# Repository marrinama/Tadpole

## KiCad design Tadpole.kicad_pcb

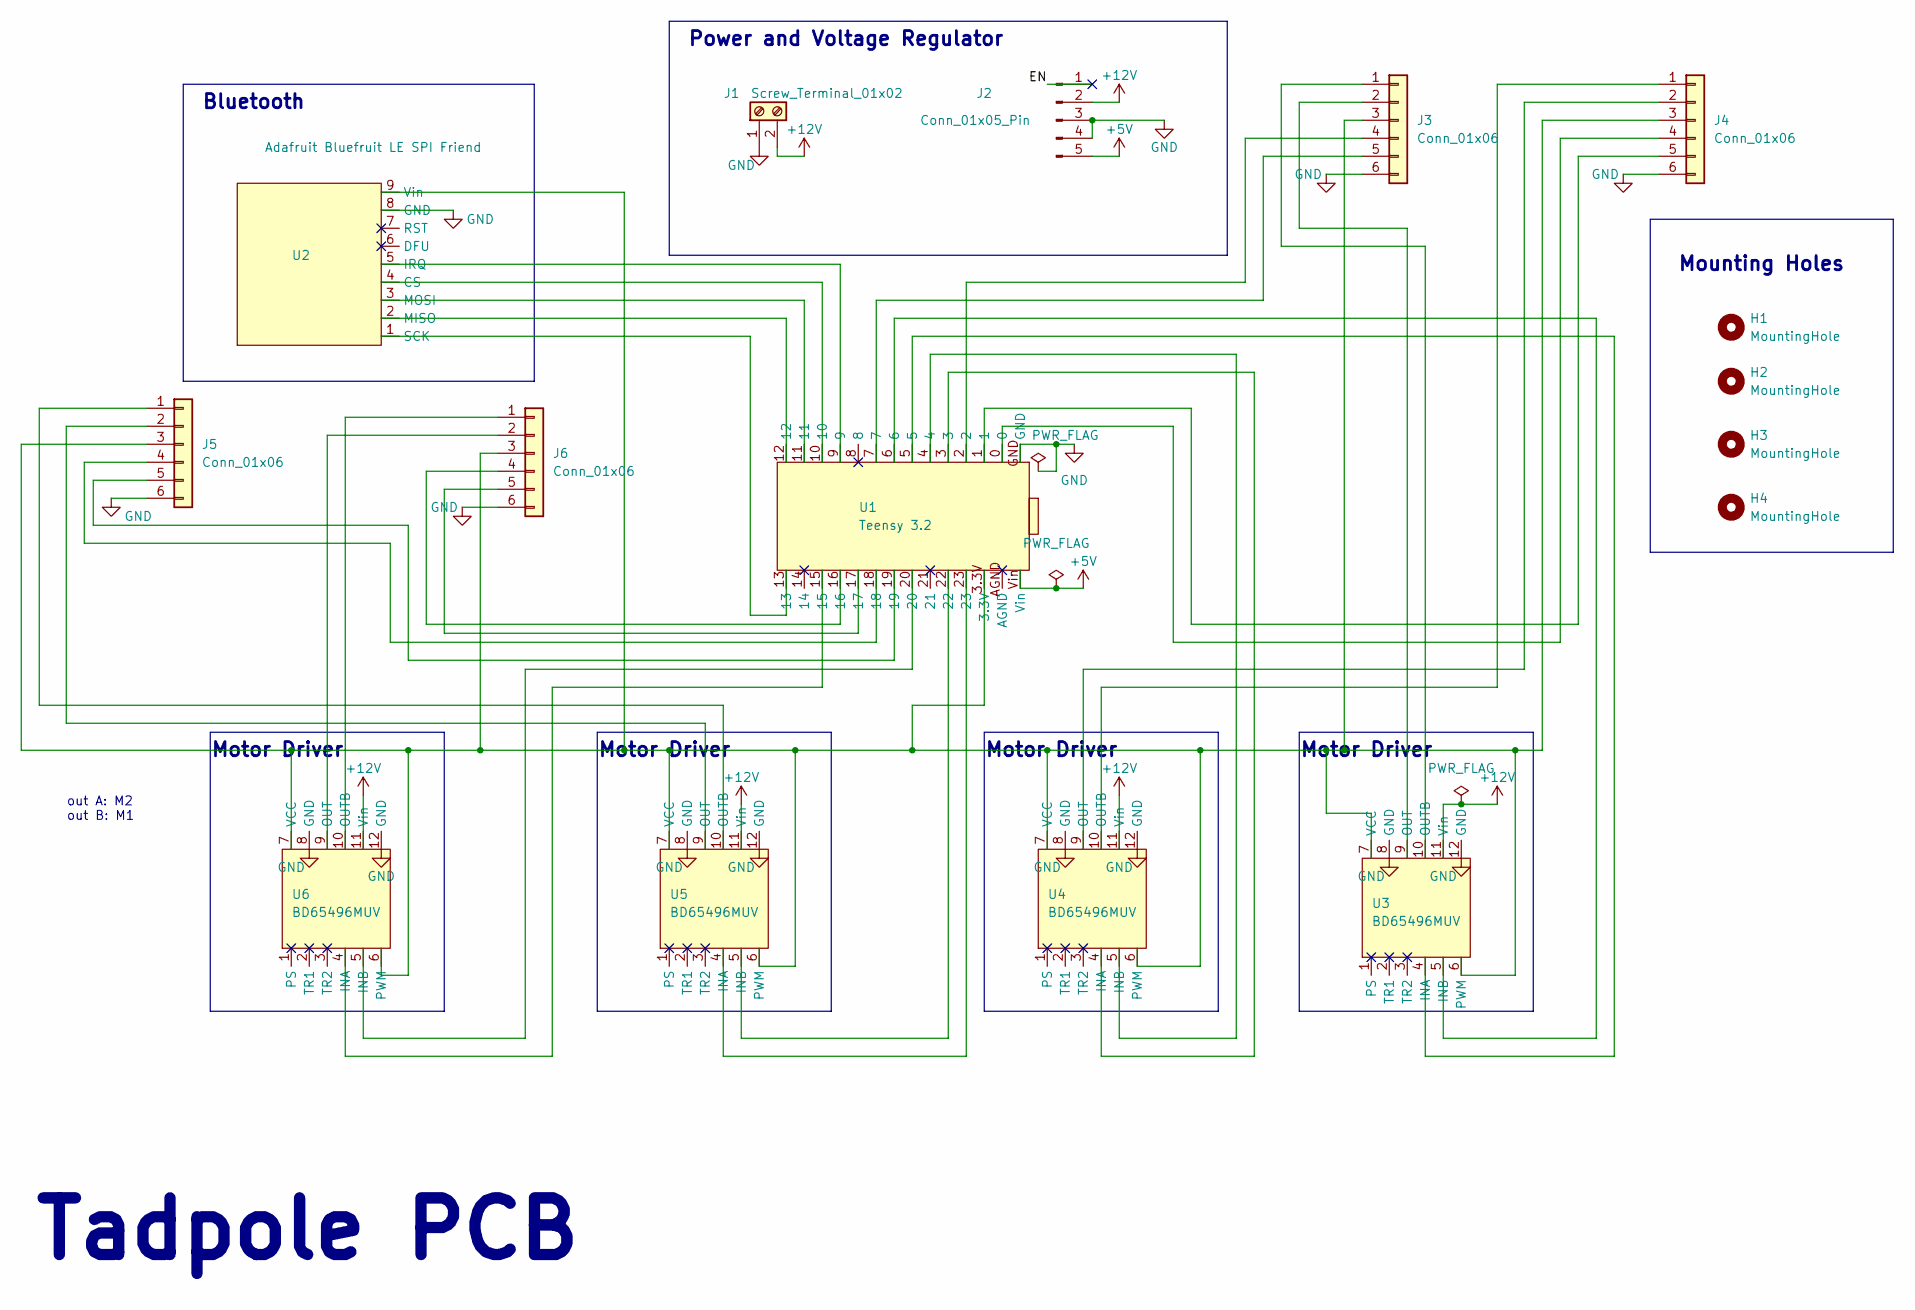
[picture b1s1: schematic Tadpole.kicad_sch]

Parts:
H1, H2, H3, H4: MountingHole; MountingHole_2.2mm_M2_DIN965_Pad
J1: Screw_Terminal_01x02; AMASS_XT30U-M_1x02_P5.0mm_Vertical
J2: Conn_01x05_Pin; PinHeader_1x05_P2.54mm_Vertical
J3, J4, J5, J6: Conn_01x06; PinHeader_1x06_P2.54mm_Vertical
U1: Teensy 3.2; teensy
U2: Adafruit Bluefruit LE SPI Friend
U3, U4, U5, U6: BD65496MUV

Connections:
+5V: J2.5, U1.Vin
+12V: J1.2, J2.2, U3.11 (Vin), U4.11 (Vin), U5.11 (Vin), U6.11 (Vin)
/EN: J2.1
GND: J1.1, J2.3, J2.4, J3.6, J4.6, J5.6, J6.6, U1.GND, U2.8 (GND), U3.8 (GND), U3.12 (GND), U4.8 (GND), U4.12 (GND), U5.8 (GND), U5.12 (GND), U6.8 (GND), U6.12 (GND)
unnamed: J3.1, U3.10 (OUTB)
unnamed: J3.2, U3.9 (OUT)
unnamed: J3.3, J4.3, J5.3, J6.3, U1.3.3V, U2.9 (Vin), U3.6 (PWM), U3.7 (VCC), U4.6 (PWM), U4.7 (VCC), U5.6 (PWM), U5.7 (VCC), U6.6 (PWM), U6.7 (VCC)
unnamed: J3.4, U1.2
unnamed: J3.5, U1.7
unnamed: J4.1, U4.10 (OUTB)
unnamed: J4.2, U4.9 (OUT)
unnamed: J4.4, U1.0
unnamed: J4.5, U1.1
unnamed: J5.1, U5.10 (OUTB)
unnamed: J5.2, U5.9 (OUT)
unnamed: J5.4, U1.18
unnamed: J5.5, U1.19
unnamed: J6.1, U6.10 (OUTB)
unnamed: J6.2, U6.9 (OUT)
unnamed: J6.4, U1.16
unnamed: J6.5, U1.17
unnamed: U1.10, U2.4 (CS)
unnamed: U1.9, U2.5 (IRQ)
unnamed: U1.12, U2.2 (MISO)
unnamed: U1.11, U2.3 (MOSI)
unnamed: U1.13, U2.1 (SCK)
unnamed: U1.5, U3.4 (INA)
unnamed: U1.6, U3.5 (INB)
unnamed: U1.3, U4.4 (INA)
unnamed: U1.4, U4.5 (INB)
unnamed: U1.23, U5.4 (INA)
unnamed: U1.22, U5.5 (INB)
unnamed: U1.15, U6.4 (INA)
unnamed: U1.20, U6.5 (INB)

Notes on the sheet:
Bluetooth
Tadpole PCB
Motor Driver
Mounting Holes
Power and Voltage Regulator
out A: M2 out B: M1

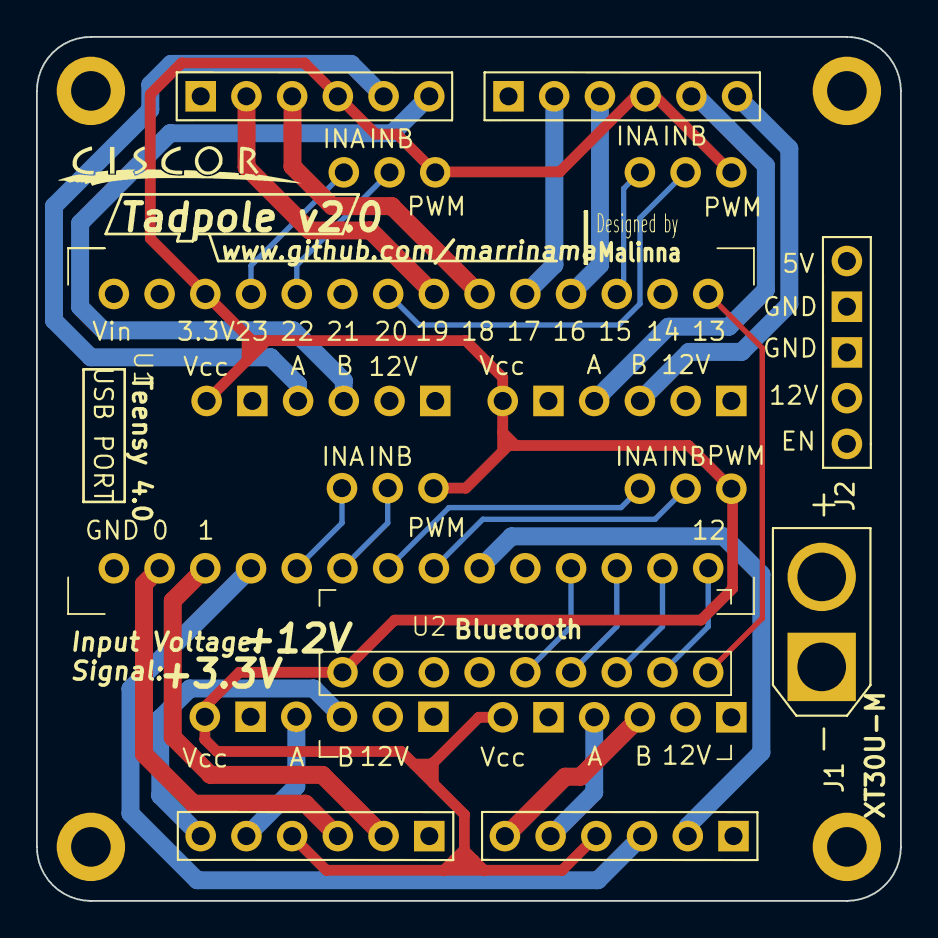
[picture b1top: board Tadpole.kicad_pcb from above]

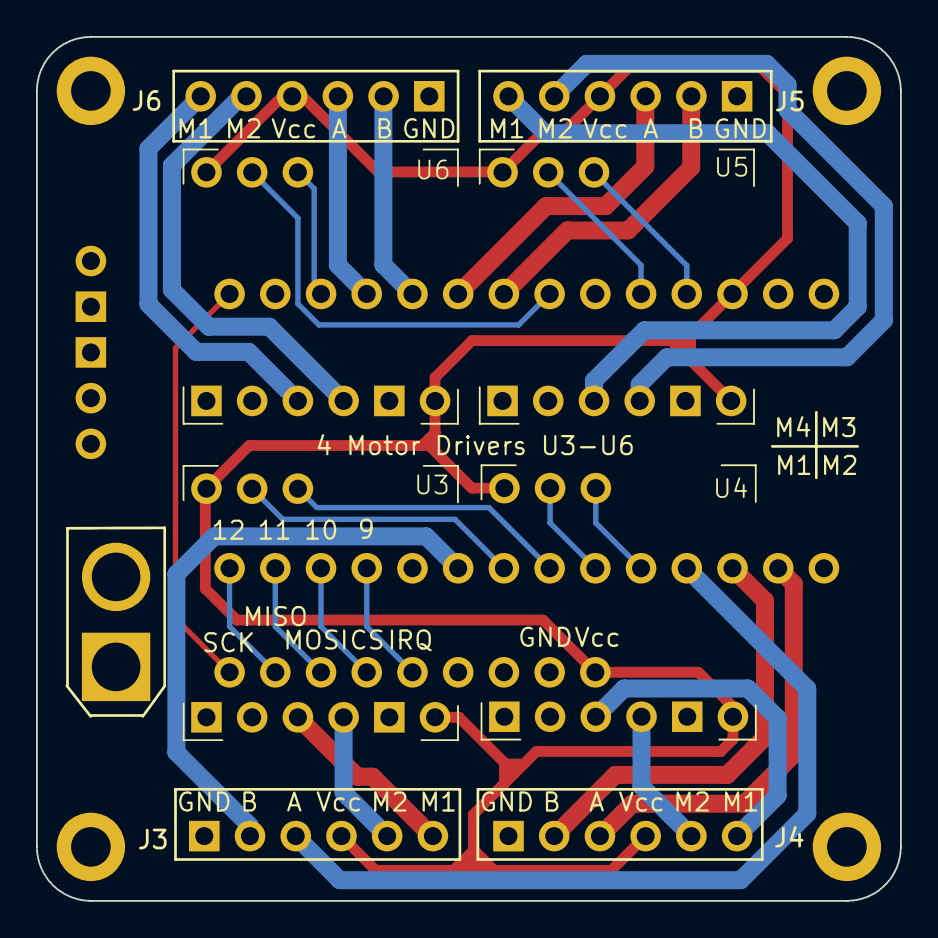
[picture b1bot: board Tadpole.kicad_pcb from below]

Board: 4 copper layers, 48.0 x 48.0 mm, 16 parts (4 on the bottom side), 33 nets.
